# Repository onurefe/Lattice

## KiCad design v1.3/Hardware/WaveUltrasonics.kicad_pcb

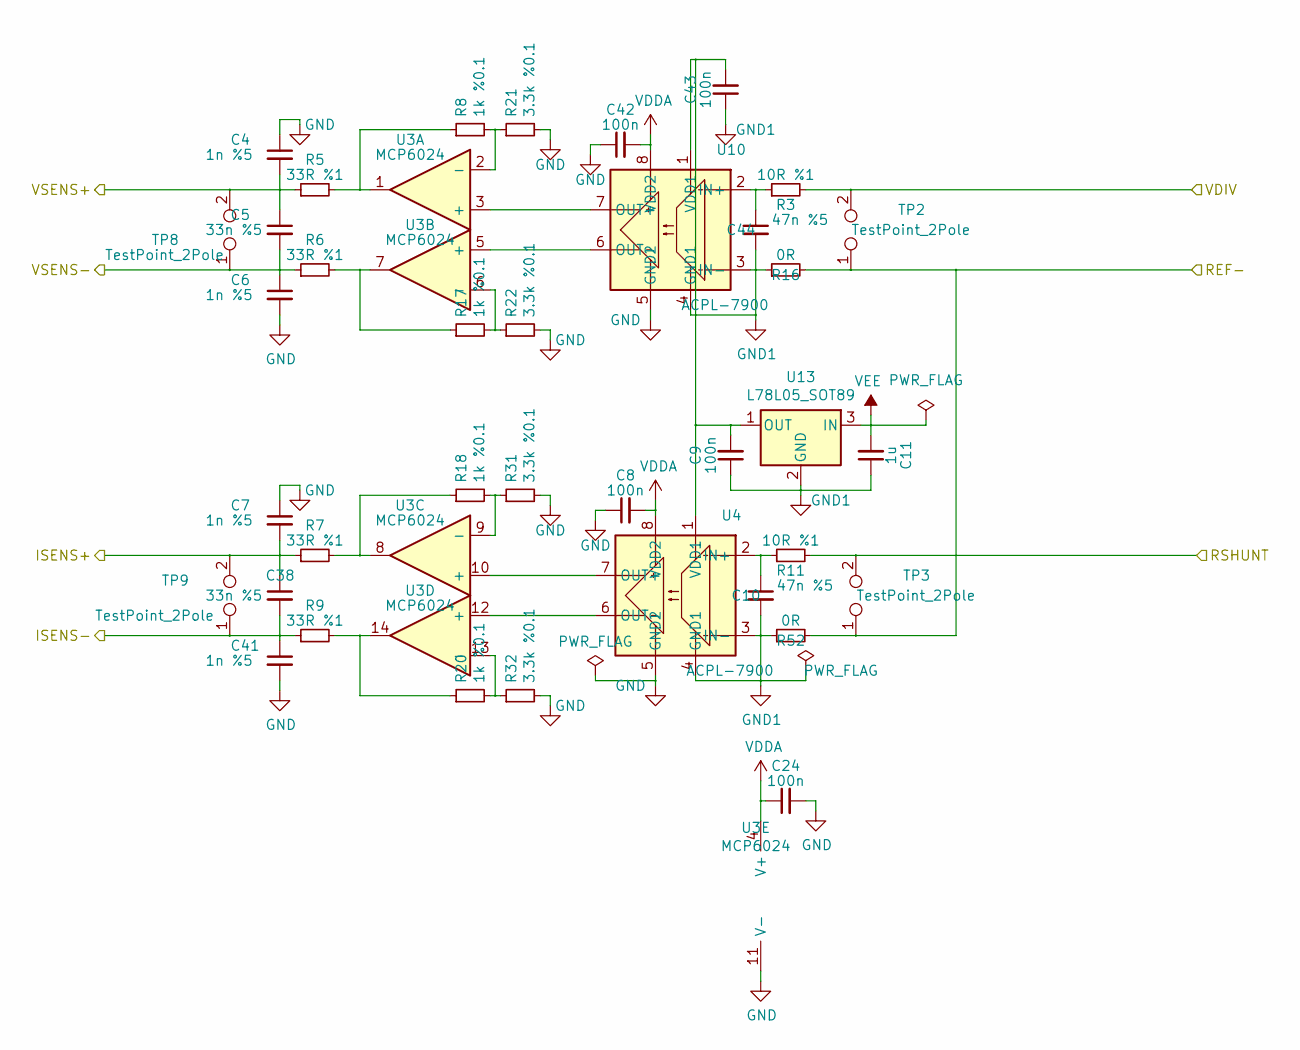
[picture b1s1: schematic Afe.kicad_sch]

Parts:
C4, C6, C7, C41: 1n %5; C_0805_2012Metric
C5, C38: 33n %5; C_0805_2012Metric
C8, C9, C24, C42, C43: 100n; C_0805_2012Metric
C10, C44: 47n %5; C_1206_3216Metric
C11: 1u; C_0805_2012Metric
R3, R11: 10R %1; R_0805_2012Metric
R5, R6, R7, R9: 33R %1; R_0805_2012Metric
R8, R17, R18, R20: 1k %0.1; R_0805_2012Metric
R16, R52: 0R; R_0805_2012Metric
R21, R22, R31, R32: 3.3k %0.1; R_0805_2012Metric
TP2, TP3, TP8, TP9: TestPoint_2Pole; PinHeader_1x02_P2.54mm_Vertical
U3: MCP6024; SOIC-14_3.9x8.7mm_P1.27mm
U4, U10: ACPL-7900; SSO-8_6.7x9.8mm_P2.54mm_Clearance8mm
U13: L78L05_SOT89; SOT-89-3

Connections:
/ISENS+: C7.2, C38.1, R7.1, TP9.2; also elsewhere on the board
/ISENS-: C38.2, C41.1, R9.1, TP9.1; also elsewhere on the board
/RSHUNT: R11.2, TP3.2; also elsewhere on the board
/VDIV: R3.2, TP2.2; also elsewhere on the board
/VSENS+: C4.2, C5.1, R5.1, TP8.2; also elsewhere on the board
/VSENS-: C5.2, C6.1, R6.1, TP8.1; also elsewhere on the board
Earth_Protective: R16.2, R52.2, TP2.1, TP3.1; also elsewhere on the board
GND: C4.1, C6.2, C7.1, C8.1, C24.2, C41.2, C42.1, R21.2, R22.2, R31.2, R32.2, U3.11 (V-), U4.5 (GND2), U10.5 (GND2); also elsewhere on the board
GND1: C9.1, C10.2, C11.1, C43.1, C44.2, R16.1, R52.1, U4.3 (IN-), U4.4 (GND1), U10.3 (IN-), U10.4 (GND1), U13.2 (GND); also elsewhere on the board
unnamed: C10.1, R11.1, U4.2 (IN+)
unnamed: C9.2, C43.2, U4.1 (VDD1), U10.1 (VDD1), U13.1 (OUT)
unnamed: C44.1, R3.1, U10.2 (IN+)
unnamed: R5.2, R8.1, U3.1
unnamed: R6.2, R17.1, U3.7
unnamed: R17.2, R22.1, U3.6 (-)
unnamed: R7.2, R18.1, U3.8
unnamed: R18.2, R31.1, U3.9 (-)
unnamed: R9.2, R20.1, U3.14
unnamed: R20.2, R32.1, U3.13 (-)
unnamed: R8.2, R21.1, U3.2 (-)
unnamed: U3.10 (+), U4.7 (OUT+)
unnamed: U3.12 (+), U4.6 (OUT-)
unnamed: U3.5 (+), U10.6 (OUT-)
unnamed: U3.3 (+), U10.7 (OUT+)
VDDA: C8.2, C24.1, C42.2, U3.4 (V+), U4.8 (VDD2), U10.8 (VDD2); also elsewhere on the board
VEE: C11.2, U13.3 (IN); also elsewhere on the board

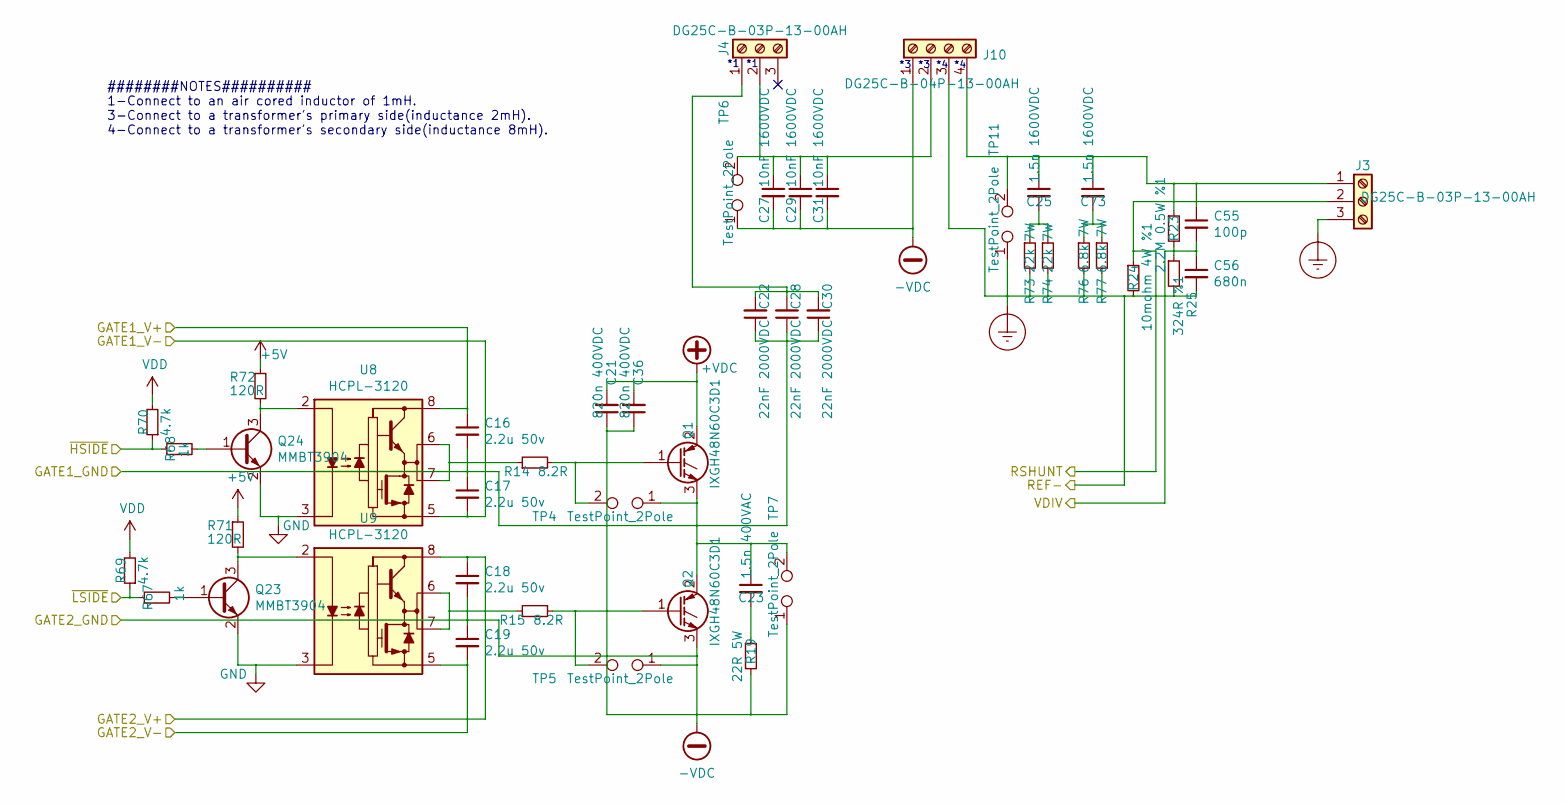
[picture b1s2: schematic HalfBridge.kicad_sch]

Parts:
C16, C17, C18, C19: 2.2u 50v; C_0805_2012Metric
C21, C36: 820n 400VDC; C_Rect_L24.0mm_W10.1mm_P22.50mm_MKT
C22, C28, C30: 22nF 2000VDC; C_Rect_L26.5mm_W10.5mm_P22.50mm_MKS4
C23: 1.5n 400VAC; C_Rect_L18.0mm_W5.0mm_P15.00mm_FKS3_FKP3
C25, C73: 1.5n 1600VDC; C_Rect_L18.0mm_W5.0mm_P15.00mm_FKS3_FKP3
C27, C29, C31: 10nF 1600VDC; C_Rect_L18.0mm_W6.0mm_P15.00mm_FKS3_FKP3
C55: 100p; C_1210_3225Metric
C56: 680n; C_0805_2012Metric
J3, J4: DG25C-B-03P-13-00AH
J10: DG25C-B-04P-13-00AH
Q1, Q2: IXGH48N60C3D1; TO-247-3_Vertical
Q23, Q24: MMBT3904; SOT-23
R14, R15: 8.2R; R_1206_3216Metric
R19: 22R 5W; R_Axial_Power_L25.0mm_W9.0mm_P30.48mm
R23: 2.2M 0.5W %1; R_1812_4532Metric
R24: 10mohm 4W %1; R_2512_6332Metric
R25: 324R %1; R_0805_2012Metric
R67, R68: 1k; R_0805_2012Metric
R69, R70: 4.7k; R_0805_2012Metric
R71, R72: 120R; R_0805_2012Metric
R73, R74: 22k 7W; R_Axial_DIN0922_L20.0mm_D9.0mm_P30.48mm_Horizontal
R76, R77: 6.8k 7W; R_Axial_Power_L25.0mm_W9.0mm_P30.48mm
TP4, TP5, TP6, TP7, TP11: TestPoint_2Pole; PinHeader_1x02_P2.54mm_Vertical
U8, U9: HCPL-3120; DIP-8_W7.62mm

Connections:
+5V: R71.1, R72.1; also elsewhere on the board
+VDC: C21.2, C36.2, Q1.2 (C); also elsewhere on the board
-VDC: C18.2, C19.1, C21.1, C27.2, C29.2, C31.2, C36.1, J10.1, Q2.3 (E), R19.2, TP5.1, TP6.1, TP7.1; also elsewhere on the board
/GATE1_GND: C16.2, C17.1, C22.1, C23.1, C28.1, C30.1, Q1.3 (E), Q2.2 (C), TP4.1, TP7.2; also elsewhere on the board
/GATE1_V+: C16.1, U8.8 (VCC); also elsewhere on the board
/GATE1_V-: C17.2, U8.5 (VEE); also elsewhere on the board
/GATE2_V+: C18.1, U9.8 (VCC); also elsewhere on the board
/GATE2_V-: C19.2, U9.5 (VEE); also elsewhere on the board
/RSHUNT: J3.2, R24.1; also elsewhere on the board
/VDIV: C55.2, C56.1, R23.2, R25.1; also elsewhere on the board
/~HALFBRIDGE_HSIDE: R68.1, R70.1; also elsewhere on the board
/~HALFBRIDGE_LSIDE: R67.1, R69.1; also elsewhere on the board
Earth_Protective: C56.2, J3.3, J10.3, R24.2, R25.2, R73.2, R74.2, R76.2, R77.2, TP11.1; also elsewhere on the board
GND: Q23.2 (E), Q24.2 (E), U8.3 (C), U9.3 (C); also elsewhere on the board
unnamed: C22.2, C28.2, C30.2, J4.1
unnamed: C23.2, R19.1
unnamed: C25.1, C55.1, C73.1, J3.1, J10.4, R23.1, TP11.2
unnamed: C25.2, R73.1, R74.1
unnamed: C27.1, C29.1, C31.1, J4.2, J10.2, TP6.2
unnamed: C73.2, R76.1, R77.1
unnamed: Q1.1 (G), R14.2, TP4.2
unnamed: Q2.1 (G), R15.2, TP5.2
unnamed: Q23.1 (B), R67.2
unnamed: Q23.3 (C), R71.2, U9.2 (A)
unnamed: Q24.1 (B), R68.2
unnamed: Q24.3 (C), R72.2, U8.2 (A)
unnamed: R14.1, U8.6 (VO), U8.7 (VO)
unnamed: R15.1, U9.6 (VO), U9.7 (VO)
VDD: R69.2, R70.2; also elsewhere on the board

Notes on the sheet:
########NOTES########## 1-Connect to an air cored inductor of 1mH. 3-Connect to a transformer's primary side(inductance 2mH). 4-Connect to a transformer's secondary side(inductance 8mH).

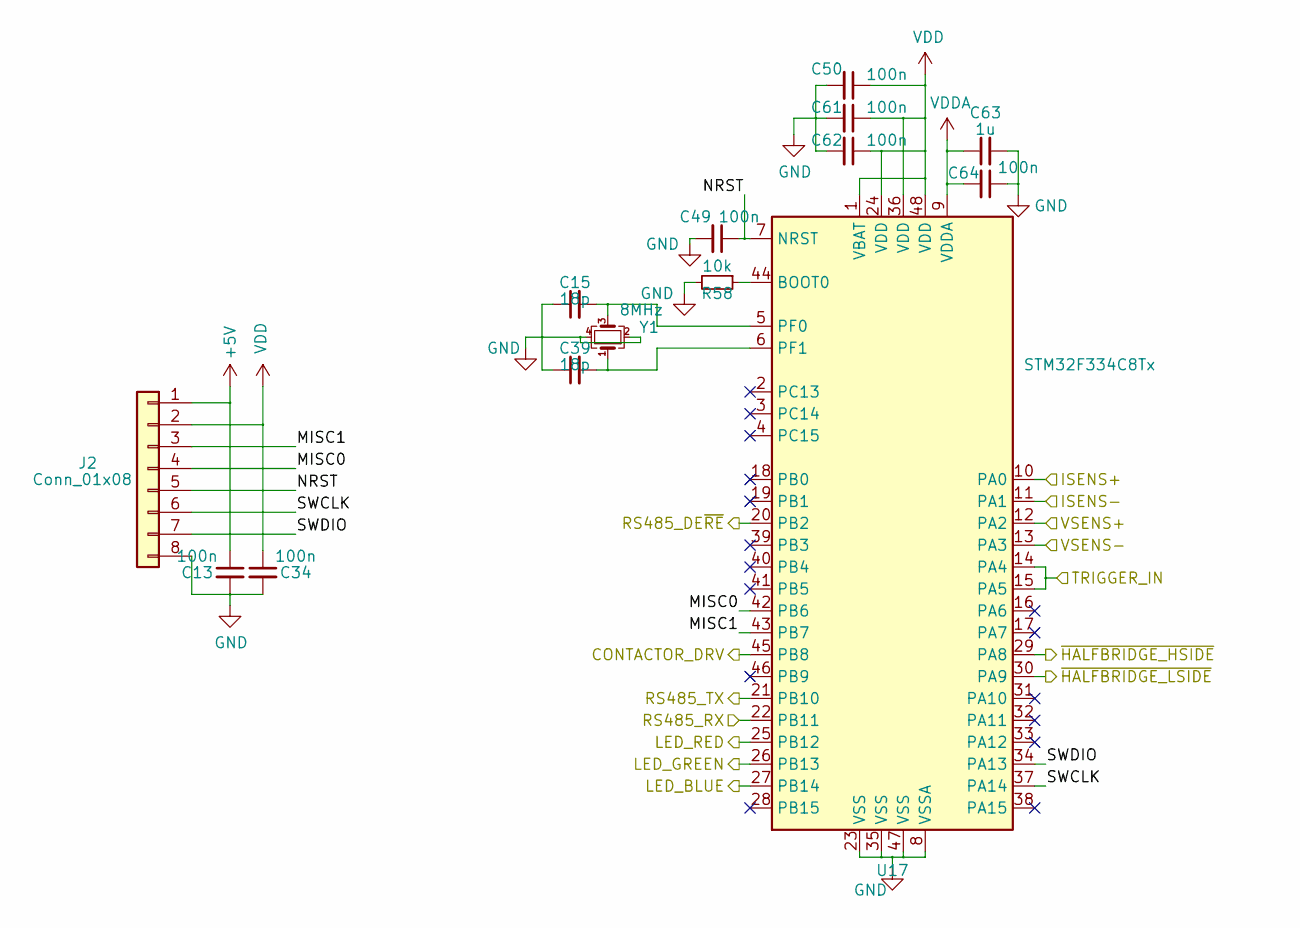
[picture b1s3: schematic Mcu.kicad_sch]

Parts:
C13, C34, C49, C50, C61, C62, C64: 100n; C_0805_2012Metric
C15, C39: 18p; C_0603_1608Metric
C63: 1u; C_0805_2012Metric
J2: Conn_01x08; PinHeader_1x08_P2.54mm_Vertical
R58: 10k; R_0805_2012Metric
U17: STM32F334C8Tx; LQFP-48_7x7mm_P0.5mm
Y1: 8MHz; Crystal_5x3.2mm_4leads

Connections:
+5V: C13.1, J2.1; also elsewhere on the board
/CONTACTOR_DRV: U17.45 (PB8); also elsewhere on the board
/ISENS+: U17.10 (PA0); also elsewhere on the board
/ISENS-: U17.11 (PA1); also elsewhere on the board
/LED_BLUE: U17.27 (PB14); also elsewhere on the board
/LED_GREEN: U17.26 (PB13); also elsewhere on the board
/LED_RED: U17.25 (PB12); also elsewhere on the board
/Mcu/MISC0: J2.4, U17.42 (PB6)
/Mcu/MISC1: J2.3, U17.43 (PB7)
/Mcu/NRST: C49.1, J2.5, U17.7 (NRST)
/Mcu/SWCLK: J2.6, U17.37 (PA14)
/Mcu/SWDIO: J2.7, U17.34 (PA13)
/RS485_DE~RE: U17.20 (PB2); also elsewhere on the board
/RS485_RX: U17.22 (PB11); also elsewhere on the board
/RS485_TX: U17.21 (PB10); also elsewhere on the board
/TRIGOUT: U17.14 (PA4), U17.15 (PA5); also elsewhere on the board
/VSENS+: U17.12 (PA2); also elsewhere on the board
/VSENS-: U17.13 (PA3); also elsewhere on the board
/~HALFBRIDGE_HSIDE: U17.29 (PA8); also elsewhere on the board
/~HALFBRIDGE_LSIDE: U17.30 (PA9); also elsewhere on the board
GND: C13.2, C15.1, C34.2, C39.1, C49.2, C50.2, C61.2, C62.2, C63.2, C64.1, J2.8, R58.2, U17.8 (VSSA), U17.23 (VSS), U17.35 (VSS), U17.47 (VSS), Y1.2, Y1.4; also elsewhere on the board
unnamed: C15.2, U17.5 (PF0), Y1.3
unnamed: C39.2, U17.6 (PF1), Y1.1
unnamed: R58.1, U17.44 (BOOT0)
VDD: C34.1, C50.1, C61.1, C62.1, J2.2, U17.1 (VBAT), U17.24 (VDD), U17.36 (VDD), U17.48 (VDD); also elsewhere on the board
VDDA: C63.1, C64.2, U17.9 (VDDA); also elsewhere on the board

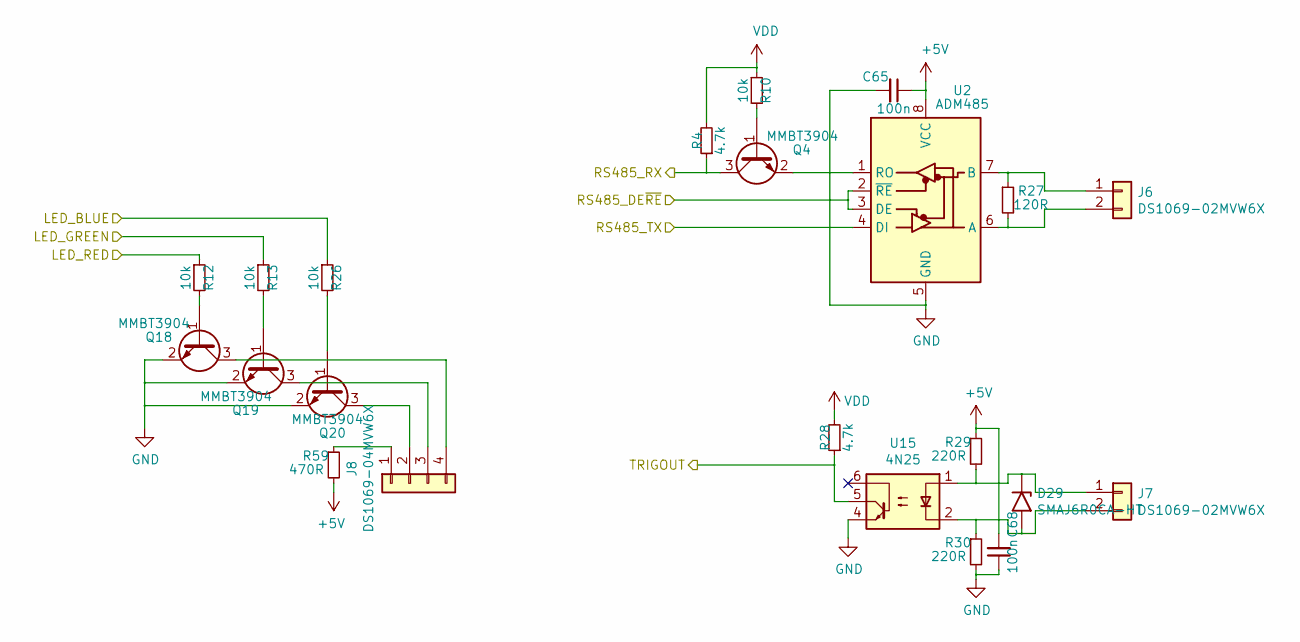
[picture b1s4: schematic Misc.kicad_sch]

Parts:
C65, C68: 100n; C_0805_2012Metric
D29: SMAJ6R0CA-HT; DO214AC_SMA
J6, J7: DS1069-02MVW6X; JST_EH_B2B-EH-A_1x02_P2.50mm_Vertical
J8: DS1069-04MVW6X; JST_EH_B4B-EH-A_1x04_P2.50mm_Vertical
Q4, Q18, Q19, Q20: MMBT3904; SOT-23
R4, R28: 4.7k; R_0805_2012Metric
R10, R12, R13, R26: 10k; R_0805_2012Metric
R27: 120R; R_0805_2012Metric
R29, R30: 220R; R_0805_2012Metric
R59: 470R; R_0805_2012Metric
U2: ADM485; SOIC-8_3.9x4.9mm_P1.27mm
U15: 4N25; DIP-6_W7.62mm

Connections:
+5V: C65.1, C68.2, R29.1, R59.2, U2.8 (VCC); also elsewhere on the board
/LED_BLUE: R26.1; also elsewhere on the board
/LED_GREEN: R13.1; also elsewhere on the board
/LED_RED: R12.1; also elsewhere on the board
/RS485_DE~RE: U2.2 (~RE), U2.3 (DE); also elsewhere on the board
/RS485_RX: Q4.3 (C), R4.1; also elsewhere on the board
/RS485_TX: U2.4 (DI); also elsewhere on the board
/TRIGOUT: R28.1, U15.5; also elsewhere on the board
GND: C65.2, C68.1, Q18.2 (E), Q19.2 (E), Q20.2 (E), R30.2, U2.5 (GND), U15.4; also elsewhere on the board
unnamed: D29.1 (A1), J7.1, R29.2, U15.1
unnamed: D29.2 (A2), J7.2, R30.1, U15.2
unnamed: J6.1, R27.1, U2.7 (B)
unnamed: J6.2, R27.2, U2.6 (A)
unnamed: J8.1, R59.1
unnamed: J8.2, Q20.3 (C)
unnamed: J8.3, Q19.3 (C)
unnamed: J8.4, Q18.3 (C)
unnamed: Q4.1 (B), R10.2
unnamed: Q4.2 (E), U2.1 (RO)
unnamed: Q18.1 (B), R12.2
unnamed: Q19.1 (B), R13.2
unnamed: Q20.1 (B), R26.2
VDD: R4.2, R10.1, R28.2; also elsewhere on the board

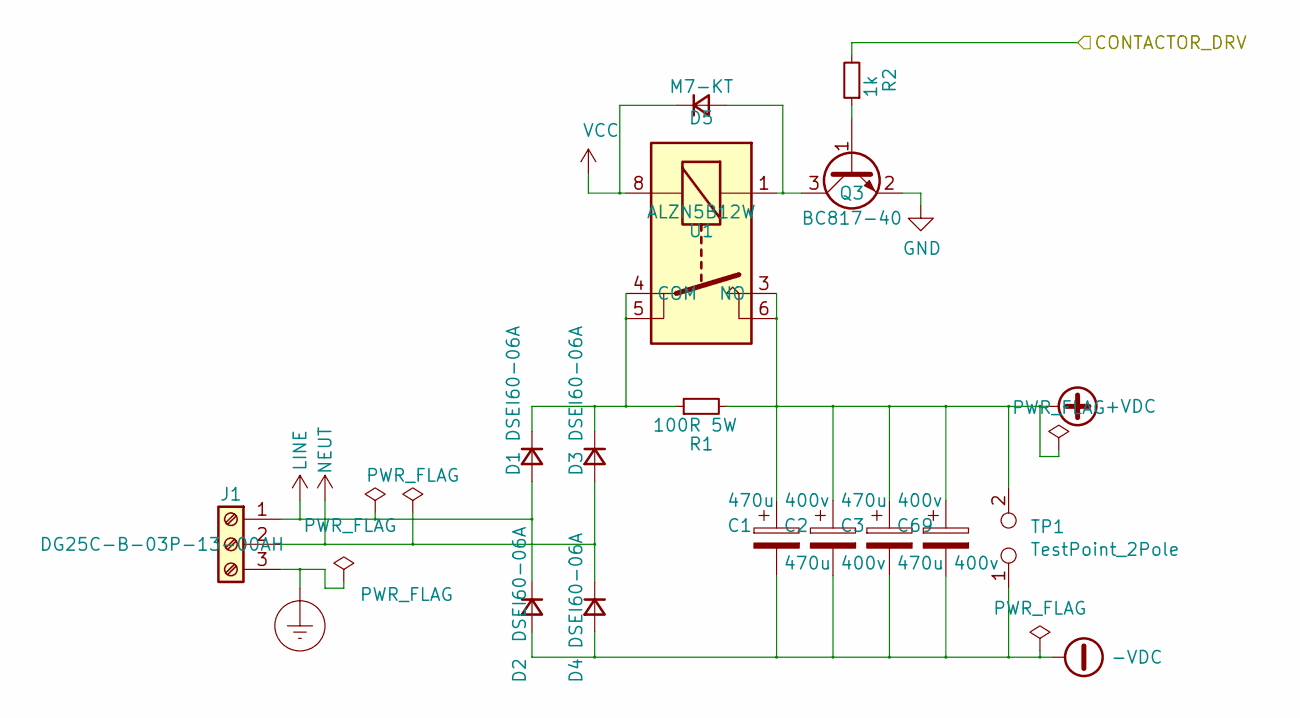
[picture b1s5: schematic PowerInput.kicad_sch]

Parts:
C1, C2, C3, C69: 470u 400v; CP_Radial_D35.0mm_P10.00mm_SnapIn
D1, D2, D3, D4: DSEI60-06A; TO-247-2_Vertical
D5: M7-KT; D_SMA
J1: DG25C-B-03P-13-00AH
Q3: BC817-40; SOT-23
R1: 100R 5W; R_Axial_Power_L25.0mm_W9.0mm_P30.48mm
R2: 1k; R_0805_2012Metric
TP1: TestPoint_2Pole; PinHeader_1x02_P2.54mm_Vertical
U1: ALZN5B12W

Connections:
+VDC: C1.1, C2.1, C3.1, C69.1, R1.2, TP1.2, U1.3 (NO), U1.6; also elsewhere on the board
-VDC: C1.2, C2.2, C3.2, C69.2, D2.2 (A), D4.2 (A), TP1.1; also elsewhere on the board
/CONTACTOR_DRV: R2.2; also elsewhere on the board
Earth_Protective: J1.3; also elsewhere on the board
GND: Q3.2 (E); also elsewhere on the board
LINE: D1.2 (A), D2.1 (K), J1.1; also elsewhere on the board
NEUT: D3.2 (A), D4.1 (K), J1.2; also elsewhere on the board
unnamed: D1.1 (K), D3.1 (K), R1.1, U1.4 (COM), U1.5
unnamed: D5.2 (A), Q3.3 (C), U1.1
unnamed: Q3.1 (B), R2.1
VCC: D5.1 (K), U1.8; also elsewhere on the board

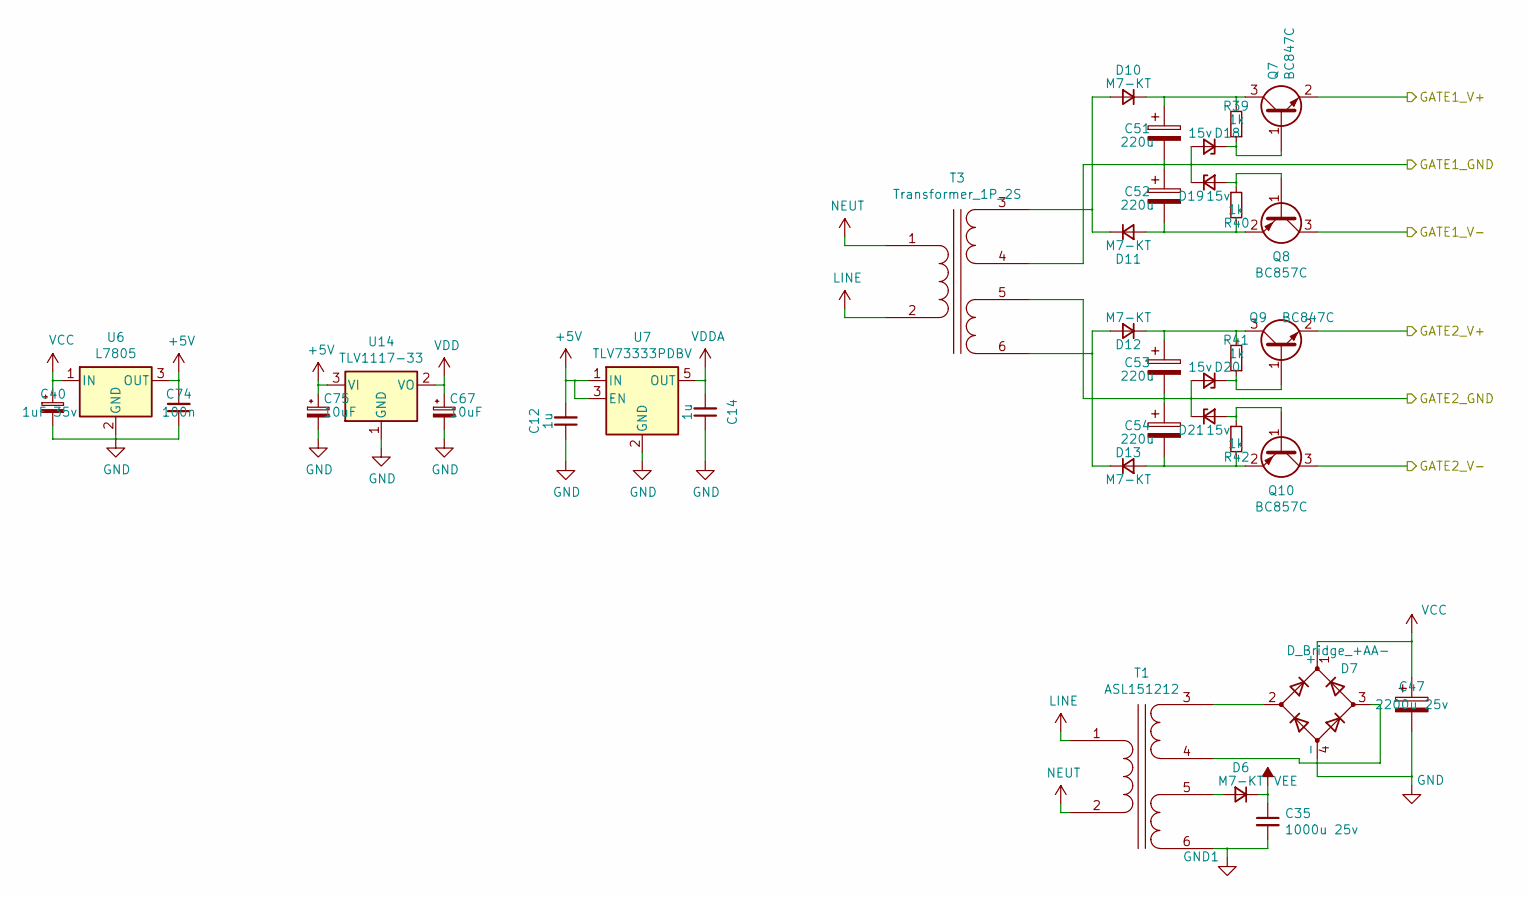
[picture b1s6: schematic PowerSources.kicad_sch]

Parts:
C12, C14: 1u; C_0805_2012Metric
C35: 1000u 25v; CP_Radial_D10.0mm_P5.00mm
C40: 1uF 35v; C_1206_3216Metric
C47: 2200u 25v; CP_Radial_D13.0mm_P5.00mm
C51, C52, C53, C54: 220u; CP_Radial_D6.3mm_P2.50mm
C67, C75: 10uF; CP_EIA-6032-15_Kemet-U
C74: 100n; C_0805_2012Metric
D6, D10, D11, D12, D13: M7-KT; D_SMA
D7: D_Bridge_+AA-; Diode_Bridge_Vishay_KBU
D18, D19, D20, D21: 15v; D_SOD-123
Q7, Q9: BC847C; SOT-23
Q8, Q10: BC857C; SOT-23
R39, R40, R41, R42: 1k; R_0805_2012Metric
T1: ASL151212
T3: Transformer_1P_2S; ASL102212
U6: L7805; TO-252-2
U7: TLV73333PDBV; SOT-23-5
U14: TLV1117-33; SOT-223-3_TabPin2

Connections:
+5V: C12.2, C74.2, C75.1, U6.3 (OUT), U7.1 (IN), U7.3 (EN), U14.3 (VI); also elsewhere on the board
-VDC: C53.2, C54.1, D20.2 (A), D21.1 (K), T3.5 (SC); also elsewhere on the board
/GATE1_GND: C51.2, C52.1, D18.2 (A), D19.1 (K), T3.4 (SB); also elsewhere on the board
/GATE1_V+: Q7.2 (E); also elsewhere on the board
/GATE1_V-: Q8.3 (C); also elsewhere on the board
/GATE2_V+: Q9.2 (E); also elsewhere on the board
/GATE2_V-: Q10.3 (C); also elsewhere on the board
GND: C12.1, C14.1, C40.2, C47.2, C67.2, C74.1, C75.2, D7.4 (-), U6.2 (GND), U7.2 (GND), U14.1 (GND); also elsewhere on the board
GND1: C35.2, T1.6 (SD); also elsewhere on the board
LINE: T1.1 (AA), T3.2 (AB); also elsewhere on the board
NEUT: T1.2 (AB), T3.1 (AA); also elsewhere on the board
unnamed: C51.1, D10.1 (K), Q7.3 (C), R39.2
unnamed: C52.2, D11.2 (A), Q8.2 (E), R40.2
unnamed: C53.1, D12.1 (K), Q9.3 (C), R41.2
unnamed: C54.2, D13.2 (A), Q10.2 (E), R42.2
unnamed: D6.2 (A), T1.5 (SC)
unnamed: D7.2 (~~), T1.3 (SA)
unnamed: D7.3 (~~), T1.4 (SB)
unnamed: D10.2 (A), D11.1 (K), T3.3 (SA)
unnamed: D12.2 (A), D13.1 (K), T3.6 (SD)
unnamed: D18.1 (K), Q7.1 (B), R39.1
unnamed: D19.2 (A), Q8.1 (B), R40.1
unnamed: D20.1 (K), Q9.1 (B), R41.1
unnamed: D21.2 (A), Q10.1 (B), R42.1
VCC: C40.1, C47.1, D7.1 (+), U6.1 (IN); also elsewhere on the board
VDD: C67.1, U14.2 (VO); also elsewhere on the board
VDDA: C14.2, U7.5 (OUT); also elsewhere on the board
VEE: C35.1, D6.1 (K); also elsewhere on the board

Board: 2 copper layers, 171 parts (0 on the bottom side), 99 nets, no tracks yet.

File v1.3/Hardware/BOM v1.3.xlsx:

Component(s) | Value | Link | Price | Quantity
> C1-C3, C69 | 470u 400v | https://ozdisan.com/passive-components/capacitors/aluminum-c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 | 3.43189 | 4 | 13.72756
> C5, C38 | 33n %5 | https://ozdisan.com/passive-components/capacitors/smt-smd-an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 | 0.02538 | 2 | 0.05076
> C4, C6, C7, C41 | 1n %5 | https://ozdisan.com/passive-components/capacitors/smt-smd-an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 | 0.0161 | 4 | 0.0644
> C11, C12, C14, C63 | 1u | https://ozdisan.com/passive-components/capacitors/smt-smd-an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 | 0.02159 | 4 | 0.08636
> C16-C19 | 2.2u 50v | https://ozdisan.com/passive-components/capacitors/smt-smd-an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 | 0.0588 | 4 | 0.2352
> C20, C21, C36, C37 | 820n 400VDC | https://ozdisan.com/passive-components/capacitors/film-capac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 | 0.11041 | 4 | 0.44164
C23 | 1.5n 400VAC | https://ozdisan.com/passive-components/capacitors/film-capac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 | 0.1181 | 1 | 0.1181
> C27, C29, C31 | 10nF 1600VDC | https://ozdisan.com/passive-components/capacitors/film-capac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 | 0.16698 | 3 | 0.50094
> C22, C28, C30 | 22nF 2000VDC | https://ozdisan.com/passive-components/capacitors/film-capac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 | 0.51486 | 3 | 1.54458
C35 | 1000u 25v | https://ozdisan.com/passive-components/capacitors/aluminum-c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 | 0.09455 | 1 | 0.09455
> C15, C39 | 18p | https://ozdisan.com/passive-components/capacitors/smt-smd-an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 | 0.00585 | 2 | 0.0117
C40 | 1uF 35v | https://ozdisan.com/passive-components/capacitors/tantalum-c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 | 0.10224 | 1 | 0.10224
> C8, C9, C13, C24, C26, C32-C34, C42, C43, C49, C50, C61, C62, C64, C65, C68, 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 | 100n | https://ozdisan.com/passive-components/capacitors/smt-smd-an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 | 0.01537 | 18 | 0.27666
> C10, C44 | 47n %5 | https://ozdisan.com/passive-components/capacitors/smt-smd-an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 | 0.03867 | 2 | 0.07734
C47 | 2200u 25v | https://ozdisan.com/passive-components/capacitors/aluminum-c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 | 0.25611 | 1 | 0.25611
> C51-C54 | 220u | https://ozdisan.com/passive-components/capacitors/aluminum-c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 | 0.02782 | 4 | 0.11128
C55 | 100p | https://ozdisan.com/passive-components/capacitors/smt-smd-an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 | 0.30671 | 1 | 0.30671
C56 | 680n | https://ozdisan.com/passive-components/capacitors/smt-smd-an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 | 0.03123 | 1 | 0.03123
> C25, C73 | 1.5n 1600VDC | https://ozdisan.com/passive-components/capacitors/film-capac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 | 0.1181 | 2 | 0.2362
> C67, C75 | 10uF | https://ozdisan.com/passive-components/capacitors/tantalum-c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 | 0.25116 | 2 | 0.50232
> D1-D4 | DSEI60-06A | https://ozdisan.com/Product/Detail/2822/DSEI60-06A | 3.15062 | 4 | 12.60248
> D5, D6, D10-D13 | M7-KT | https://ozdisan.com/power-semiconductors/diodes-diode-module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 | 0.01131 | 6 | 0.06786
D7 | D_Bridge_+AA- | https://www.ozdisan.com/power-semiconductors/diodes-diode-mo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 | 0.29222 | 1 | 0.29222
> D18-D21 | 15v | https://ozdisan.com/power-semiconductors/diodes-diode-module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 | 0.0266 | 4 | 0.1064
D29 | SMAJ6R0CA-HT | https://ozdisan.com/power-semiconductors/diodes-diode-module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 | 0.09784 | 1 | 0.09784
> J1, J3, J4 | DG25C-B-03P-13-00AH | https://ozdisan.com/connectors-and-interconnects/terminal-bl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 | 0.27554 | 3 | 0.82662
J2 | Conn_01x05 | https://ozdisan.com/connectors-and-interconnects/headers/pin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 | 0.02281 | 1 | 0.02281
J5 | Conn_01x08 | https://ozdisan.com/connectors-and-interconnects/headers/pin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 | 0.03843 | 1 | 0.03843
> J6, J7 | DS1069-02MVW6X | https://ozdisan.com/connectors-and-interconnects/rectangular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 | 0.00702 | 2 | 0.01404
J8 | DS1069-04MVW6X | https://ozdisan.com/Product/Detail/347998/DS1069-04MVW6X | 0.01305 | 1 | 0.01305
J10 | DG25C-B-04P-13-00AH | https://ozdisan.com/Product/Detail/442582/DG25C-B-04P-13-00AH | 0.41193 | 1 | 0.41193
> Q1, Q2 | IXGH48N60C3D1 | https://www.ozdisan.com/power-semiconductors/igbts/discrete-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 | 3.94031 | 2 | 7.88062
Q3 | BC817-40 | https://ozdisan.com/power-semiconductors/transistors/discret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 | 0.02086 | 1 | 0.02086
> Q7, Q9 | BC847C | https://ozdisan.com/power-semiconductors/transistors/discret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 | 0.01623 | 2 | 0.03246
> Q8, Q10 | BC857C | https://ozdisan.com/power-semiconductors/transistors/discret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 | 0.01696 | 2 | 0.03392
> Q18-Q20, Q23, Q24 | MMBT3904 | https://ozdisan.com/Product/Detail/451907/MMBT3904LT1G | 0.01281 | 5 | 0.06405
R1 | 100R 5W | https://ozdisan.com/passive-components/resistors/tht-through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 | 0.16618 | 1 | 0.16618
R2 | 1k | https://ozdisan.com/passive-components/resistors/smt-smd-and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 | 0.00221 | 1 | 0.00221
> R3, R11 | 10R %1 | https://ozdisan.com/passive-components/resistors/smt-smd-and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 | 0.02574 | 2 | 0.05148
> R5-R7, R9 | 33R %1 | https://ozdisan.com/passive-components/resistors/smt-smd-and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 | 0.00286 | 4 | 0.01144
> R12, R13, R26, R58 | 10k | https://ozdisan.com/passive-components/resistors/smt-smd-and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 | 0.00221 | 4 | 0.00884
> R14, R15 | 8.2R | https://ozdisan.com/passive-components/resistors/smt-smd-and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 | 0.00364 | 2 | 0.00728
> R16, R52 | 0R | https://ozdisan.com/passive-components/resistors/smt-smd-and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 | 0.00221 | 2 | 0.00442
> R8, R17, R18, R20 | 1k %0.1 | https://ozdisan.com/passive-components/resistors/smt-smd-and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 | 0.00286 | 4 | 0.01144
R19 | 22R 5W | https://ozdisan.com/passive-components/resistors/tht-through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 | 0.15928 | 1 | 0.15928
> R21, R22, R31, R32 | 3.3k %0.1 | https://ozdisan.com/passive-components/resistors/smt-smd-and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 | 0.09028 | 4 | 0.36112
R23 | 2.2M 0.5W %1 | https://ozdisan.com/passive-components/resistors/smt-smd-and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 | 0.05136 | 1 | 0.05136
R24 | 10mohm 4W %1 | https://ozdisan.com/passive-components/resistors/precision-p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 | 0.93093 | 1 | 0.93093
R25 | 324R %1 | https://ozdisan.com/passive-components/resistors/smt-smd-and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 | 0.00286 | 1 | 0.00286
> R28, R69, R70 | 4.7k | https://ozdisan.com/passive-components/resistors/smt-smd-and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 | 0.00286 | 3 | 0.00858
> R29, R30 | 220R | https://ozdisan.com/passive-components/resistors/smt-smd-and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 | 0.00221 | 2 | 0.00442
R59 | 470R | https://ozdisan.com/passive-components/resistors/smt-smd-and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 | 0.00221 | 1 | 0.00221
> R39-R42, R67, R68 | 1k | https://ozdisan.com/passive-components/resistors/smt-smd-and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 | 0.00221 | 6 | 0.01326
> R71, R72 | 120R | https://ozdisan.com/passive-components/resistors/smt-smd-and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 | 0.00741 | 2 | 0.01482
> R73, R74 | 22k 7W | https://ozdisan.com/passive-components/resistors/tht-through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 | 0.19746 | 2 | 0.39492
> R76, R77 | 6.8k 7W | https://ozdisan.com/passive-components/resistors/tht-through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 | 0.19746 | 2 | 0.39492
T1 | ASL151212 | https://ozdisan.com/passive-components/transformers/general-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 | 5.13524 | 1 | 5.13524
T3 | Transformer_1P_2S | https://ozdisan.com/passive-components/transformers/general-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 | 2.43089 | 1 | 2.43089
> TP1-TP9, TP11 | TestPoint_2Pole | https://ozdisan.com/connectors-and-interconnects/headers/pin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 | 0.01305 | 10 | 0.1305
U1 | ALZN5B12W | https://ozdisan.com/electromechanical-components/relays-and-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 | 1.11804 | 1 | 1.11804
U2 | MAX3485 | https://ozdisan.com/integrated-circuits-ics/interfaces-and-p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 | 1.85284 | 1 | 1.85284
U3 | MCP6024 | https://ozdisan.com/integrated-circuits-ics/linear-ics/ampli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 | 1.67706 | 1 | 1.67706
> U4, U10 | ACPL-7900 | https://ozdisan.com/Product/Detail/459212/ACPL-7900-500E | 5.40199 | 2 | 10.80398
U6 | L7805 | https://ozdisan.com/integrated-circuits-ics/power-management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 | 0.54556 | 1 | 0.54556
U7 | TLV73333PDBV | https://ozdisan.com/integrated-circuits-ics/power-management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 | 0.10431 | 1 | 0.10431
> U8, U9 | HCPL-3120 | https://ozdisan.com/optoelectronics-and-sensors/optoelectron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 | 1.77474 | 2 | 3.54948
U13 | L78L05_SOT89 | https://ozdisan.com/integrated-circuits-ics/power-management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 | 0.05185 | 1 | 0.05185
U14 | TLV1117-33 | https://ozdisan.com/integrated-circuits-ics/power-management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 | 0.42999 | 1 | 0.42999
U15 | 4N25 | https://ozdisan.com/optoelectronics-and-sensors/optoelectron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 | 0.26025 | 1 | 0.26025
U17 | STM32F334C8Tx | https://ozdisan.com/Product/Detail/493492/STM32F334C8T6 | 7.16463 | 1 | 7.16463
Y1 | 8MHz | https://ozdisan.com/passive-components/crystals-oscillators-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 | 0.50094 | 1 | 0.50094
Total cost | 79.659
